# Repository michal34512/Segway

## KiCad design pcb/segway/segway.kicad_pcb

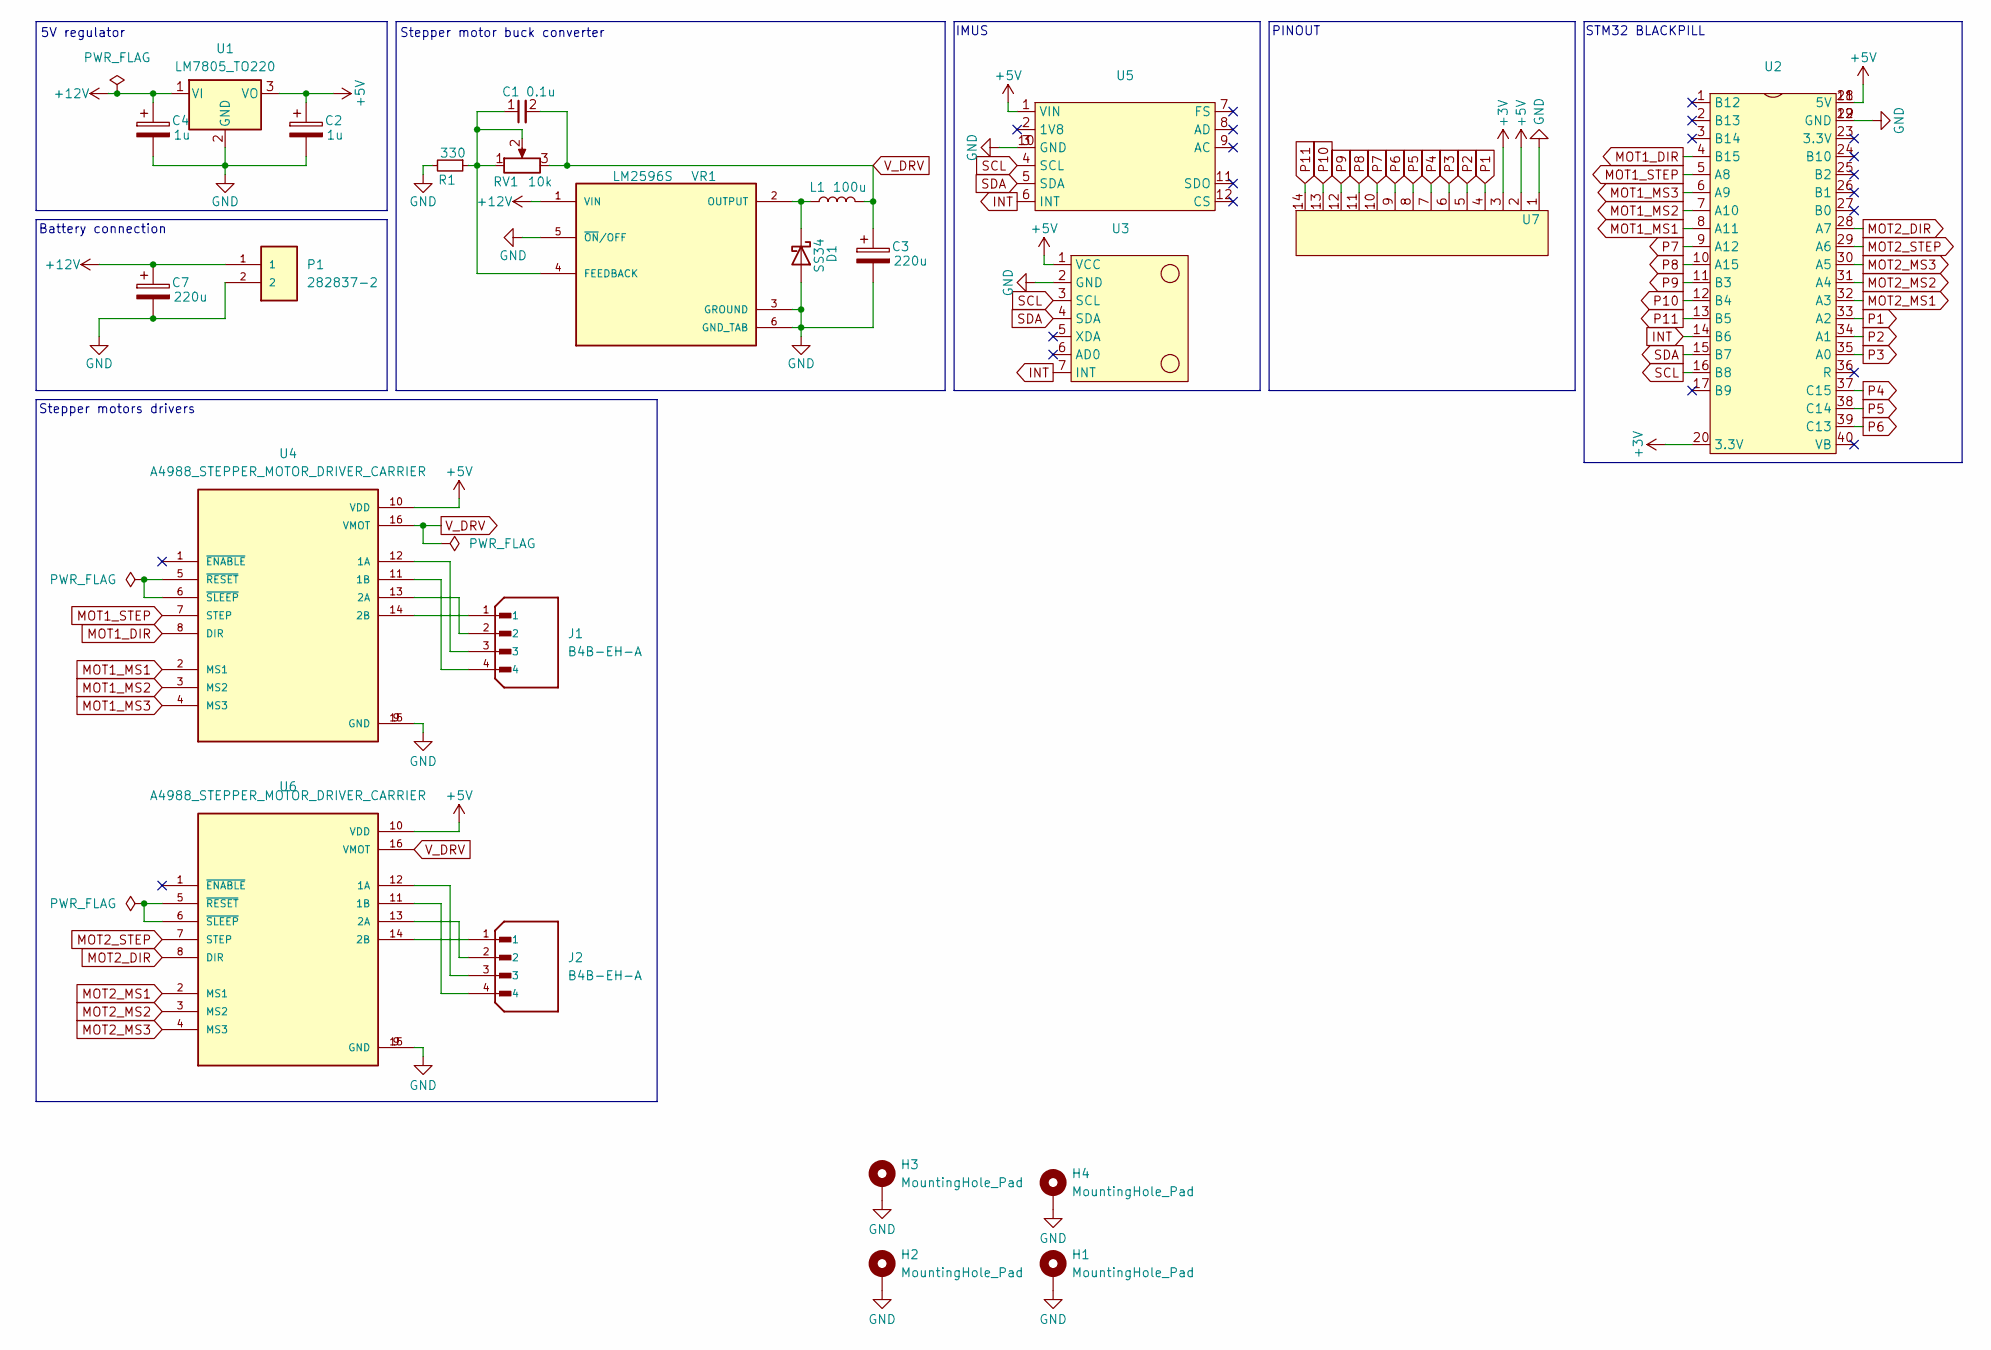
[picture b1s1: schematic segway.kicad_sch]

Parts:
C1: 0.1u; C_0402_1005Metric_Pad0.74x0.62mm_HandSolder
C2, C4: 1u; CP_Radial_D5.0mm_P2.50mm
C3, C7: 220u; CAP_EEEFPA221XAL
D1: SS34; D_1206_3216Metric_Pad1.42x1.75mm_HandSolder
H1, H2, H3, H4: MountingHole_Pad; MountingHole_3.2mm_M3_DIN965_Pad
J1, J2: B4B-EH-A; JST_B4B-EH-A
L1: 100u; INDM125125X600N
P1: 282837-2; TE_282837-2; PARTREV G3
R1: 330; R_0402_1005Metric_Pad0.72x0.64mm_HandSolder
RV1: 10k; Potentiometer_Bourns_3296W_Vertical
U1: LM7805_TO220; TO-220-3_Vertical
U2: stm32 blackpill
U3: MPU6050
U4, U6: A4988_STEPPER_MOTOR_DRIVER_CARRIER; MODULE_A4988_STEPPER_MOTOR_DRIVER_CARRIER
U5: ICN20948
U7: segway_pinout
VR1: LM2596S; TO170P1524X483-6N; PARTREV E

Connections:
+3V: U2.20 (3.3V), U7.3
+5V: C2.1, U1.3 (VO), U2.18 (5V), U2.21 (5V), U3.1 (VCC), U4.10 (VDD), U5.1 (VIN), U6.10 (VDD), U7.2
+12V: C4.1, C7.1, P1.1, U1.1 (VI), VR1.1 (VIN)
GND: C2.2, C3.2, C4.2, C7.2, D1.2 (A), H1.1, H2.1, H3.1, H4.1, P1.2, R1.2, U1.2 (GND), U2.19 (GND), U2.22 (GND), U3.2 (GND), U4.9 (GND), U4.15 (GND), U5.3 (GND), U5.10 (GND), U6.9 (GND), U6.15 (GND), U7.1, VR1.3 (GROUND), VR1.5 (~ON/OFF), VR1.6 (GND_TAB)
INT: U2.14 (B6), U3.7 (INT), U5.6 (INT)
MOT1_DIR: U2.4 (B15), U4.8 (DIR)
MOT1_MS1: U2.8 (A11), U4.2 (MS1)
MOT1_MS2: U2.7 (A10), U4.3 (MS2)
MOT1_MS3: U2.6 (A9), U4.4 (MS3)
MOT1_STEP: U2.5 (A8), U4.7 (STEP)
MOT2_DIR: U2.28 (A7), U6.8 (DIR)
MOT2_MS1: U2.32 (A3), U6.2 (MS1)
MOT2_MS2: U2.31 (A4), U6.3 (MS2)
MOT2_MS3: U2.30 (A5), U6.4 (MS3)
MOT2_STEP: U2.29 (A6), U6.7 (STEP)
unnamed: D1.1 (K), L1.1, VR1.2 (OUTPUT)
unnamed: J1.3, U4.12 (1A)
unnamed: J1.4, U4.11 (1B)
unnamed: J1.2, U4.13 (2A)
unnamed: J1.1, U4.14 (2B)
unnamed: U4.5 (~RESET), U4.6 (~SLEEP)
unnamed: J2.3, U6.12 (1A)
unnamed: J2.4, U6.11 (1B)
unnamed: J2.2, U6.13 (2A)
unnamed: J2.1, U6.14 (2B)
unnamed: U6.5 (~RESET), U6.6 (~SLEEP)
unnamed: C1.1, R1.1, RV1.1, RV1.2, VR1.4 (FEEDBACK)
P1: U2.33 (A2), U7.4
P2: U2.34 (A1), U7.5
P3: U2.35 (A0), U7.6
P4: U2.37 (C15), U7.7
P5: U2.38 (C14), U7.8
P6: U2.39 (C13), U7.9
P7: U2.9 (A12), U7.10
P8: U2.10 (A15), U7.11
P9: U2.11 (B3), U7.12
P10: U2.12 (B4), U7.13
P11: U2.13 (B5), U7.14
SCL: U2.16 (B8), U3.3 (SCL), U5.4 (SCL)
SDA: U2.15 (B7), U3.4 (SDA), U5.5 (SDA)
V_DRV: C1.2, C3.1, L1.2, RV1.3, U4.16 (VMOT), U6.16 (VMOT)

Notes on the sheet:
IMUS
5V regulator
Stepper motors drivers
STM32 BLACKPILL
Stepper motor buck converter
PINOUT
Battery connection

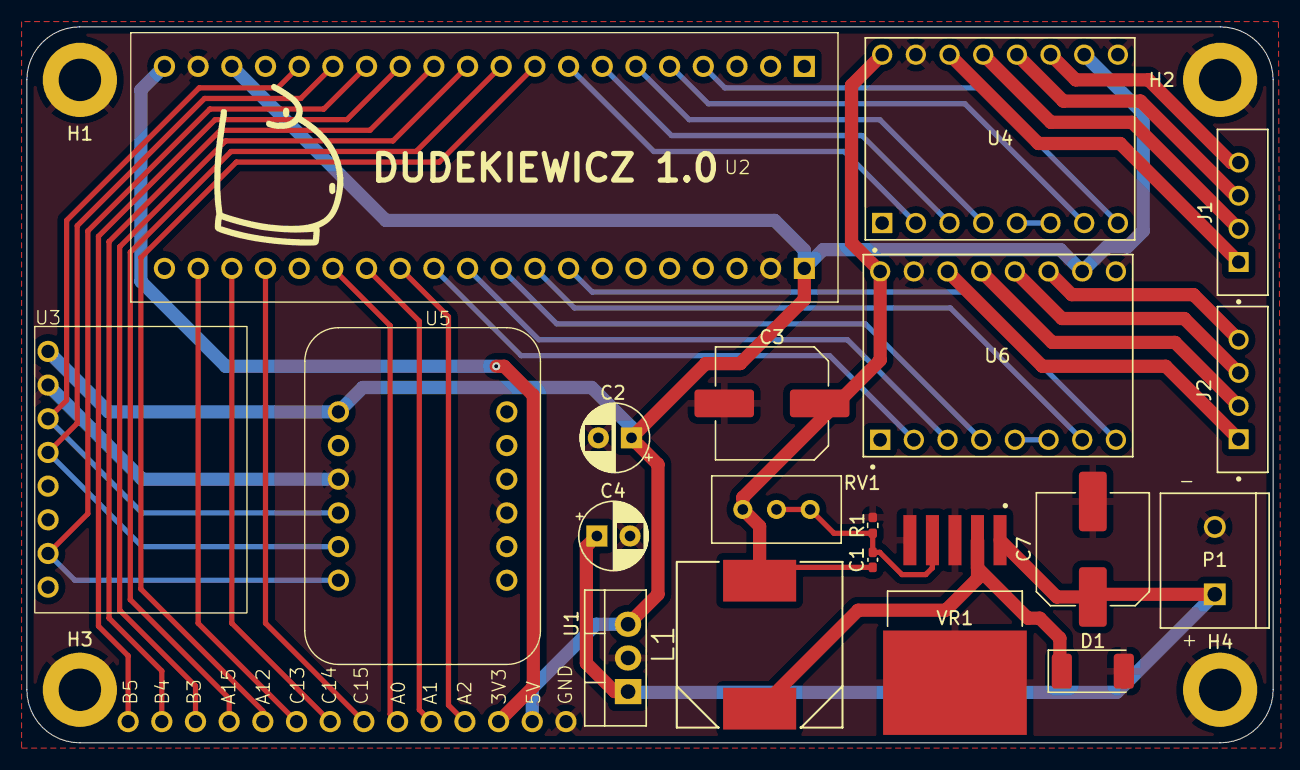
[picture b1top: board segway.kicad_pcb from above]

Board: 2 copper layers, 94.0 x 54.0 mm, 24 parts (0 on the bottom side), 41 nets.

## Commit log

2025-04-12 init
